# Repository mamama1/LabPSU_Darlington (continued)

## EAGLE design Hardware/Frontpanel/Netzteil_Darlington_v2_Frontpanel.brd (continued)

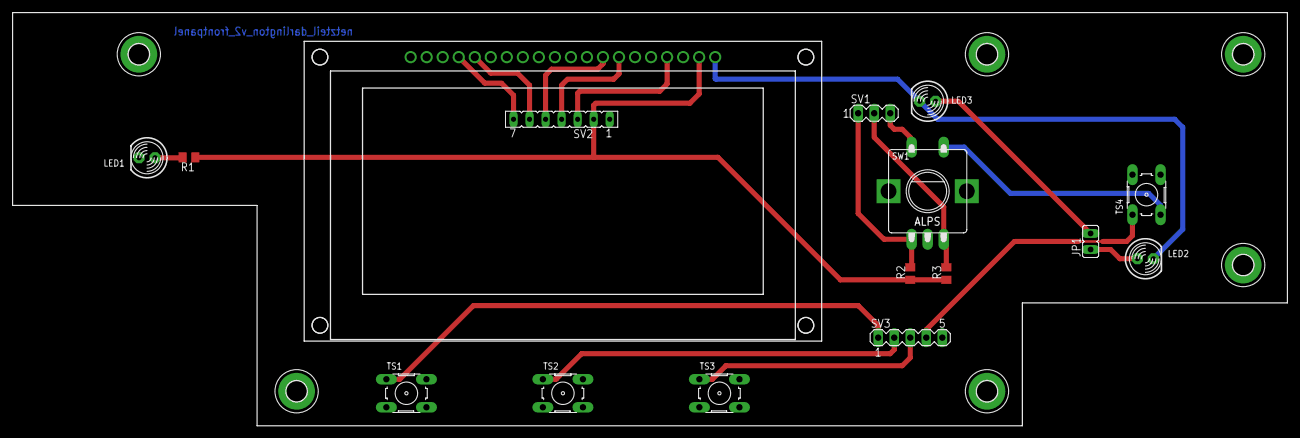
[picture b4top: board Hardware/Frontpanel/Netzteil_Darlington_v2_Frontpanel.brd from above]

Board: 2 copper layers, 202.0 x 65.5 mm, 23 parts (0 on the bottom side), 18 nets.

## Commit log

2018-11-17 Create LICENSE
2018-11-17 Create info
2018-11-17 Create tmp
2018-11-17 Add files via upload
    fix second, floating, unused ISET opamp (IC5B)
2019-01-04 update to rev 1.6
    fix several bugs and issues
2019-06-11 update to latest version
2019-07-12 repair designators, add gerber files
2019-07-21 add BOM
2019-07-21 add front panel
